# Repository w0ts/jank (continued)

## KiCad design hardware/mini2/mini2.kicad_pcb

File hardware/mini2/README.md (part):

# Jank mini 2.2: one board, two orders (USB only, or with a 1S cell), two MIDI OUTs, LINE IN with plug detect, CLOCK / RESET outs, a D-pad over 4 buttons, LEDs or a screen, u.FL (branch hw/mini2.2)

**Stage 2 + review pass 1 (2026-11-15, 72 x 72 mm): placed, routed, simulated, the fab files written; NOT ordered, NOT built, NOT measured.**
`mini2.kicad_pcb` is the routed board; `fab/` holds the Gerbers and both orders' BOM / CPL; `sim/` the simulations;
`case/` the case. Each stage's section supersedes the older ones where they differ (2, 1f, 1e, 1d, then 1c); "mini 2.2
(stage 1)" and "1b" are superseded (the encoder and the RGB LEDs are gone); everything after them is mini 2's text.

## Signoff3 (2026-11-17): round 3's fixes (`signoff2.py` again, `fatten.py`)

- **R2:** R136 is now 22 k. V5A is 4.79 V nominal, 4.58 .. 4.99 V over tolerances (the 74AHCT04 needs 4.5 V).
- **R3:** BAT_P / BAT_C / BAT_N widened up to 1 mm where room allows, with up to 3 vias at each layer change.
- **R4:** C3 is now 22 uF 25 V 0805.
- **R6:** the MIDI sinks Q10..Q13 are now AO3400A, which turn fully on from a 3.3 V gate.
- **R8:** the cell divider R10 / R11 is now 1 M / 1 M. The board drains ~9 .. 17 uA while switched off, against ~50 uA
  before. The cell reading then needs a firmware fix: board.h must read GPIO10, and the correction is affine, not an
  offset (REVIEW.md section 9).
- **R10:** R155's pads now sit 1.46 mm from the bottom edge (were 0.31 mm). R156, the same 1 ohm, is in parallel with
  it (at x 2.2, y 61.5: the only free spot): the bulk's series resistance is now 0.5 ohm, so a stiff USB cable rings VREG
  to ~5.3 V, not 5.8 V.
- **After fitting a cell,** or if the board is dead on the cell: plug USB in once. The XB5353A may hold a new cell off
  until a charger is connected, and also after a short.
- **For storage, unplug the cell.** Even switched off, the board draws a few uA from it.

## Sign-off stage 2 (2026-11-17): applied to the routed board (`signoff2.py`)

The stage-1 sign-off (`~/GitHub/jank/worktrees/mini22-review-scratch/REVIEW.md`) and its fixes:
- **R1:** C72 / C92 (2 x 100 uF) moved from VSYS to VREG, after the power switch, in both orders, behind R155 (1 ohm
  0805). Sim: VREG <= 5.16 V at switch-on and hot plug (was up to 7.9 V).
- **Inrush (usb order):** ~555 uC per plug (USB 2.0 asks 50 uC; 145 uC before). A host port's rail dips ~0.94 V for
  ~0.1 ms; another device on a bus-powered hub may reset. All of it passes R62 (0402, 0 ohm, ~14 A peak).
- **R6:** C104 (10 uF 0402) at U18's VIN. VBUS no longer runs on the bottom under U2, L4 or C5; it still skirts C3.
- **C2:** C97 / C103 added. Each LED now has its own 100 nF (C96, C97, C102, C103).
- **R5 not done:** CC2, UDP's via and CC1's via stay under J1's shell. The router found no way out (`signoff2.py`).
- **VSYS / VBUS:** with the toggle off, VSYS has no capacitance; a hot plug rings it to ~6.3 V. Add no part rated
  6 V or less there.
- **Never two cells.** J8 and J9 are in parallel before Q2 and the XB5353A. Q2 does not protect one cell from the
  other: a reversed or unequal second cell shorts or equalises through the sockets. Fit one cell in one socket.
- **Meter before soldering:** the DIN-504B (pad 2 = DIN 5, pad 4 = DIN 4), the PJ-307C (tip = pad 5) and each cell
  lead (+ on the square pad).
- **JP1 / JP2:** bridge one side only (G or V). GND is on one end and +3V3 on the other; a blob across all three pads
  shorts the rail.

## DIN-504B-M10 and PJ-320A pinouts: checked on paper (2026-11-15), confirm with a meter

Review pass 1's M5. A pinout agent checked the makers' drawings, EasyEDA's footprints, independent SDS-50J footprints
and CA-033 / DIN 41524, counting the bottom-side flip once (pictures: `~/GitHub/jank/worktrees/pinout-scratch/out/`).
Its verdict: **all correct**, so no swap jumpers.
- **DIN-504B-M10 (J5 / J6):** DIN 4 = pad 4 (the source, MD_R / MD2_R), DIN 5 = pad 2 (the sink, MD_T / MD2_T), DIN 2 =
  pad 3 (GND); pad 1 = DIN 3, pad 5 = DIN 1, pads 6 / 7 the shell.
- **PJ-320A (J13 CLOCK, J14 RESET):** the tip = contact D (CLK_OUT / RST_OUT), A = the sleeve (GND); **B is a second
  ring spring, not a switch**; C the ring.
- **PJ-307C:** the tip = pad 5, the ring = pad 2 (Type A), LINE IN's detect switch as wired.
- Still worth a meter on the first socket and jack before soldering a batch.

## Before ordering (checklist)

- The DIN / PJ-320A pinouts above: a meter on the first socket and jack.
- **JLC's placement preview** (review pass 1, LOW 9): the orientation of every IC (U1 the module, U2, U5, U6, U7, U8, U9,
  U11, U12, U15 .. U19, U21), FET (Q2 .. Q13), diode (D3, D7 .. D11, D14, D16), LED (LED1 .. LED4), L4 / L5 and J1, before paying.
- `sh case/make_stl.sh` re-run on the final board before printing (review pass 1, LOW 5: **not re-run** this round (the coordinator: the STLs come later); J4 moved under the RF line, the case reads it (`place_args.py`)).
- **Check every cell's polarity** with a meter (pin 1, the square pad, = +) before plugging it: see "a reversed cell"
  below.
- The tantalums C86 (+3V3, battery order), C27 and C91 (VBUS): JLC's preview must show their band (+) on pad 1.
- The firmware (review passes 1 and 2, updated 2026-11-15): the brown-out detector on; **the cell "empty" at 3.3 V
  under load** (the TPS63802 buck-boost holds +3V3 to the end: sim/power.py; the 3.6 V / 3.7 V rules and the 2.42"
  switch-on rule are gone with the LDO); **the USB pull-up (D+) only while VBUS_SENSE (GPIO14) is high** (Espressif's
  self-powered device rule); the cell's ADC reading calibrated once per board against a meter.
- **The firmware, 2026-11-15 (required changes):**
  - **Flash: the WROOM-1U-N8R2 has 8 MB** (+ 2 MB quad PSRAM for the heap, BLE MIDI): usbaudio's `partitions_usb.csv`
    (2 x 2 MB OTA slots + a 2 MB FAT drive, 6.1 MB) fits again; the FH4R2's 4 MB plan (streaming the drive into the spare
    slot) is no longer needed. Today's images: 1.05 MB (build-xiao), 1.28 MB with BLE.
  - **LED_DATA is GPIO38** (2026-11-15 GPIO re-map: "The GPIO map" is the pin map).
  - **The digital LINE IN** (2026-11-15): the ADC's continuous pattern at 83,333 Hz with 12 entries,
    **[tip, sense] x 5 + [tip, cell]**: tip = GPIO9 (ADC1_CH8, node A), sense = GPIO8 (ADC1_CH7, node B), cell = GPIO10
    (ADC1_CH9); ATTEN3 (0 .. 2.9 V; both nodes centred at 1.467 V). The signal is A - B: **the sense samples are skewed
    by one ADC slot against tip: correct them with a 16-tap half-sample delay filter**; **subtract each slot's own offset**
    (A and B's DC from the bias, measured with no plug or averaged); **interpolate the missing sense sample** in the
    [tip, cell] slot; an optional per-board gain calibration (A against B, a test tone on the sleeve). The tip runs at
    41.7 kHz, the sense at 34.7 kHz; the anti-alias pole 13.3 kHz (-5.4 dB at 20.8 kHz). LIN_DET (GPIO48).
  - **The RGB LEDs** (GPIO38, WS2812B-2020 GRB, 800 kHz: RMT) run from the 5 V aux rail (VLED ~4.9 V): no dropout rule.
  - **MIDI OUT: invert the UART TX** (`uart_set_line_inverse(port, UART_SIGNAL_TXD_INV)` on UART1 / GPIO37 and UART2 /
    GPIO42): the pins drive the 2N7002s of the 5 V loops (idle low = no current). Drive strength no longer matters. If
    the escape hatch back to the 3.3 V drive is used (R122 / R123, R126 .. R129), un-invert it.
  - **The 5 V aux rail** (U18, the TPS61023): **GPIO41 (V5_EN_IO) switches it**; R131 100 k to +3V3 keeps it ON while
    the pin floats (reset, boot, erased firmware). Drive it low to turn the LEDs, the MIDI loops, CLOCK / RESET and the
    host signal off (at the cell's cutoff, in sleep: `gpio_hold_en` + `gpio_deep_sleep_hold_en`, GPIO41 is not an RTC
    pin). Hatch: lift R137 (0 ohm) and the rail is on for good. Turn it off only with HOST_EN low and the LEDs dark.
    **The charge pump is gone: no LEDC on GPIO35 (pump.c), no pump warm-up**; CLK / RST can be driven at once (0 / ~4.4 V
    into 10 k, ~4.85 V into 100 k: sim/cv.txt; the user accepts it in place of the earlier "5 V+" rule).
  - **USB host mode (battery order only):** the TUSB320LI at I2C 0x47 starts as a sink (PORT low). For host mode write
    DRP + Try.SRC (MODE_SELECT, SOURCE_PREF) with DISABLE_TERM set around it (its 7.3.2 sequence); on INT (GPIO13,
    pull-up on) read ATTACHED_STATE: **Attached.SRC (a device) -> HOST_EN (GPIO47) high and the S3's USB-OTG in host
    mode; anything else (detached, Attached.SNK: a charger or a host) -> HOST_EN low first**, then device mode. V5H comes
    from the 5 V aux rail (no pump): **usbport's prep_ms ~0** (the aux rail is already up; the TPS61023's soft start is
    ~0.7 ms after the switch-on: its sheet). HOST_EN never high while unattached (Type-C: no VBUS before an attach). Device mode keeps the review-pass-2 rules (VBUS_SENSE, the D+ pull-up). The
    usb order has no U17 / Q9 (R3 / R4 / R63 fitted): device only.

## Experiment A (2026-11-15, the user's: "fewer part types, no change to how the circuit works")

On Standard every part type pays JLC's loading fee (~$1.53; the quote's $88.35 = 57 types), so the lever is the type
count. Each merge checked against the datasheets and the sims (`sim/`):

| Merge | Verdict |
|---|---|
| R51 12 k 0603 -> 0402 (C25752) | applied |
| R120 / R121 47 ohm 0603 -> 100 ohm 0402 (C25076) | applied; `cv.py` (the sleeve 100 ohm): 4.36 V into 10 k (typ), 4.79 V into 100 k |
| R40 33 -> 22 ohm (C25092) | applied |
| R88 / R89 22 k / 33 k -> 100 k / 150 k | applied; `power.py`: Q1 back on 0.30 .. 0.52 s after an unplug (was 0.16 .. 0.28: VBUS decays slower), D9 carries meanwhile, VSYS min unchanged |
| R136 18 k -> 20 k | applied: V5A 4.85 V (4.72 .. 4.97). `cv.py` 4.36 / 4.25 V into 10 k (was 4.44, the user accepted ~4.5), `midi.py` 5.24 mA typical (5.51), 3.37 mA at the worst corner (3.54), `host.py` 4.40 V into 100 k (4.46); the clamp's overlap with the boost 2 mA at most (was 7) |
| R141 56 k -> 100 k + 12 k (R146), R142 10 k -> 20 k | applied: 3.30 V, R2 20 k (TI: <= 100 k) |
| jack sources 3 x 680 -> 2 x 470; the four 220 ohm sinks -> 470 // 470 (R147 .. R150) | applied; `midi.py` above |
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
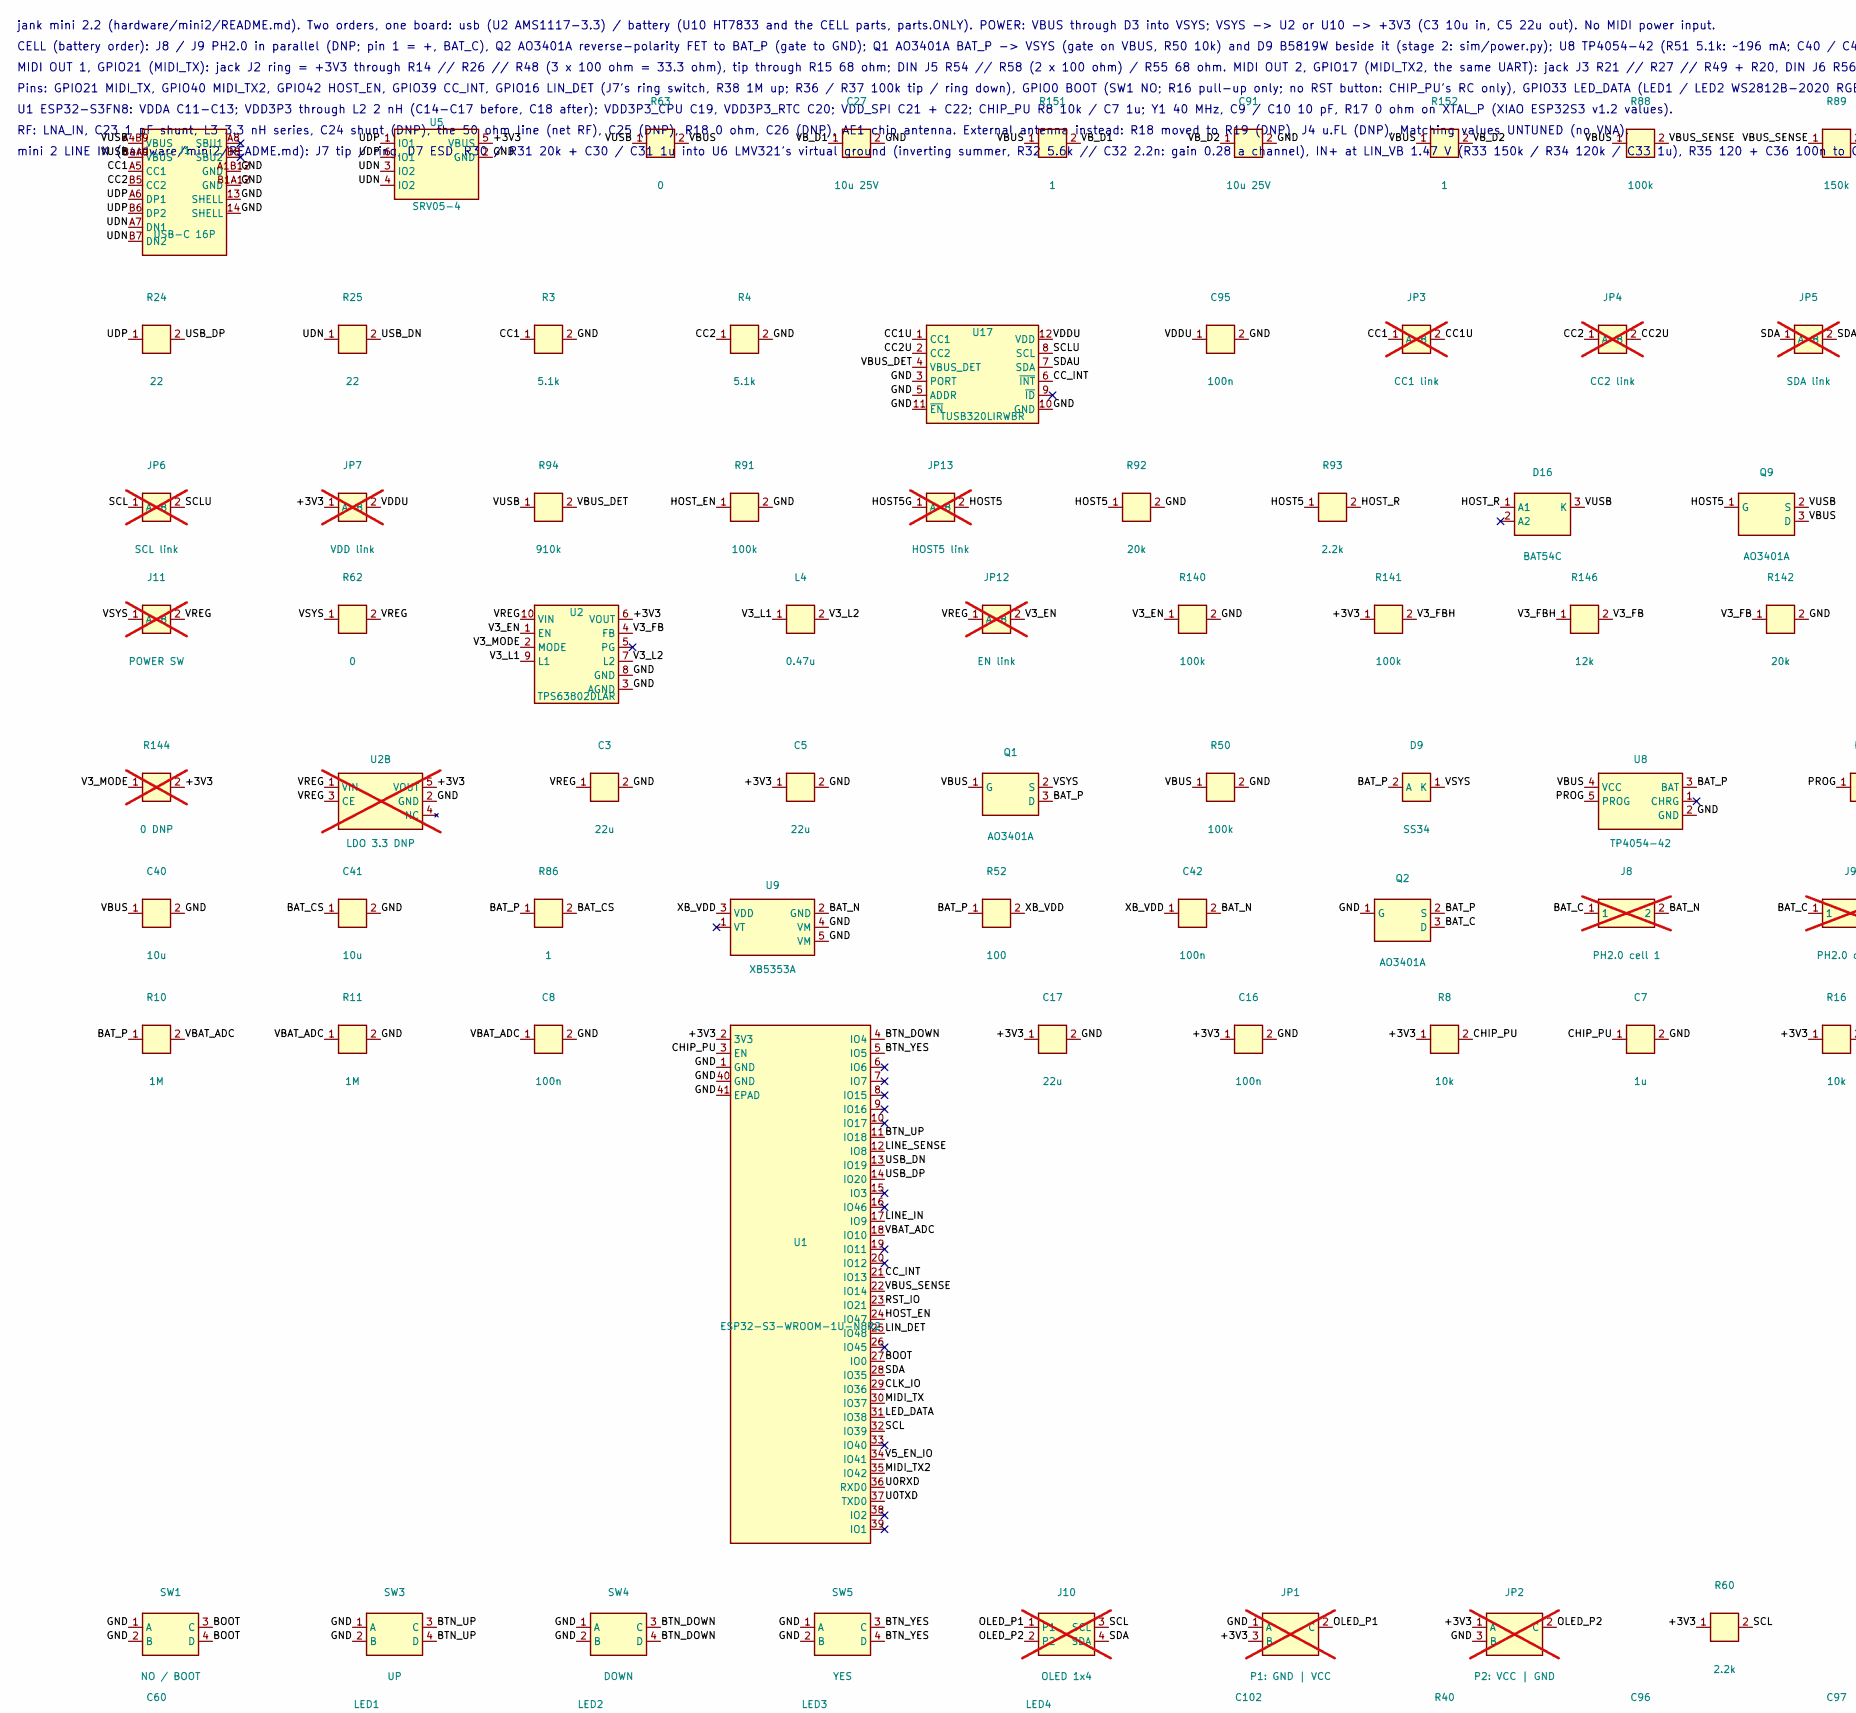
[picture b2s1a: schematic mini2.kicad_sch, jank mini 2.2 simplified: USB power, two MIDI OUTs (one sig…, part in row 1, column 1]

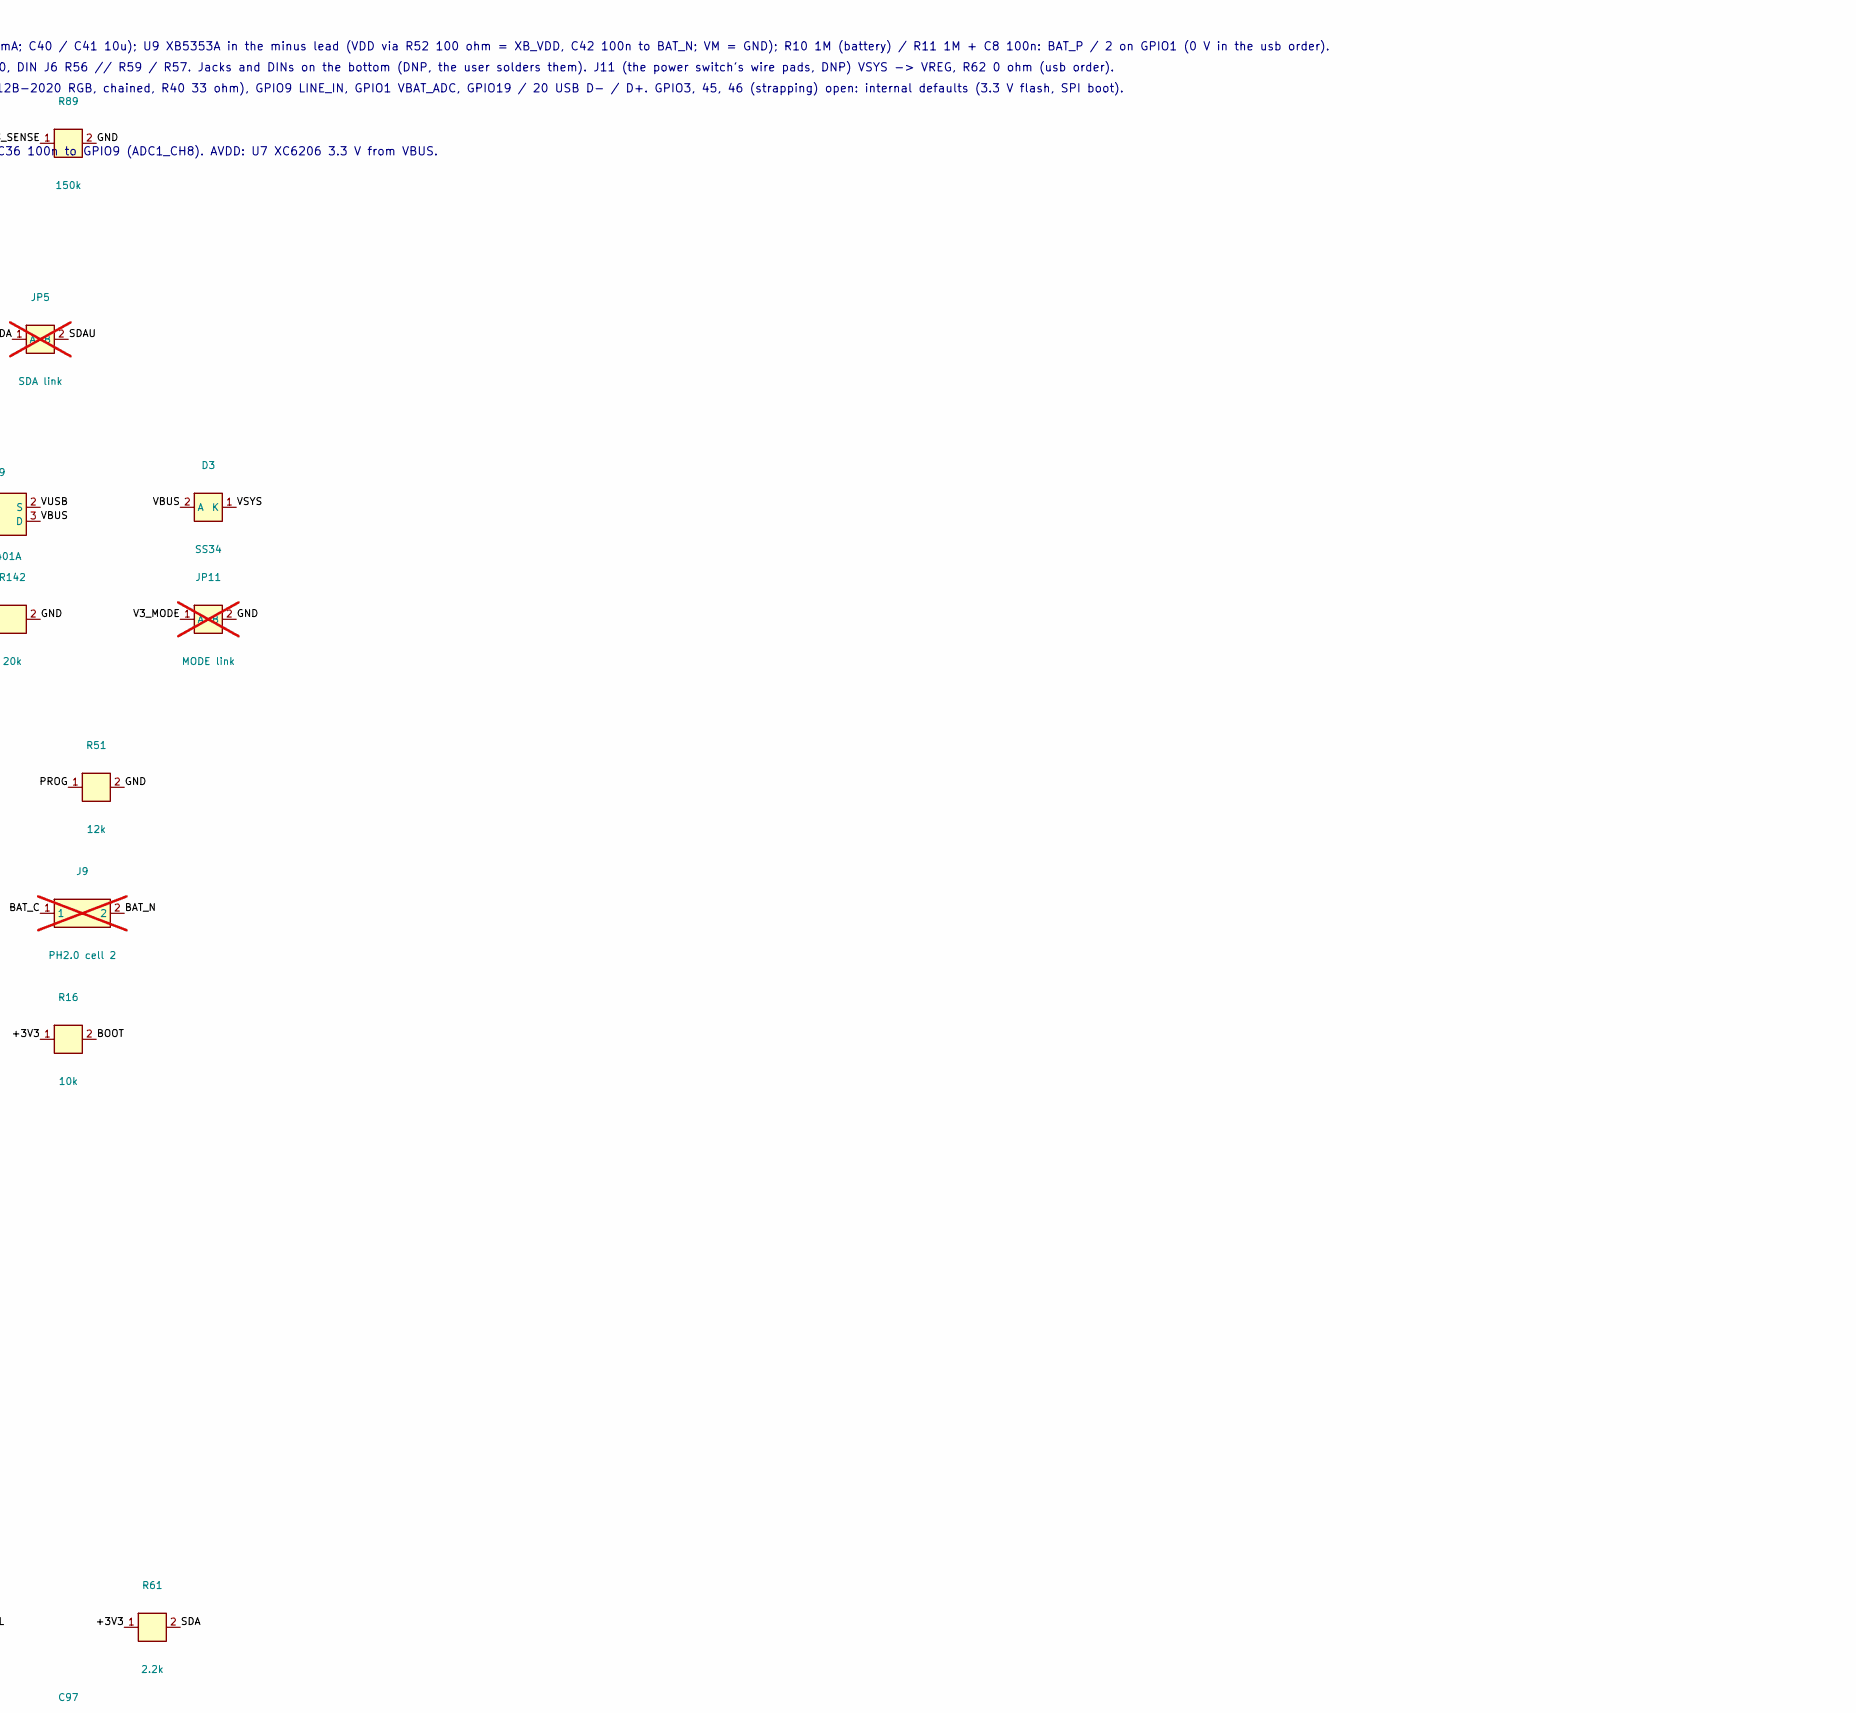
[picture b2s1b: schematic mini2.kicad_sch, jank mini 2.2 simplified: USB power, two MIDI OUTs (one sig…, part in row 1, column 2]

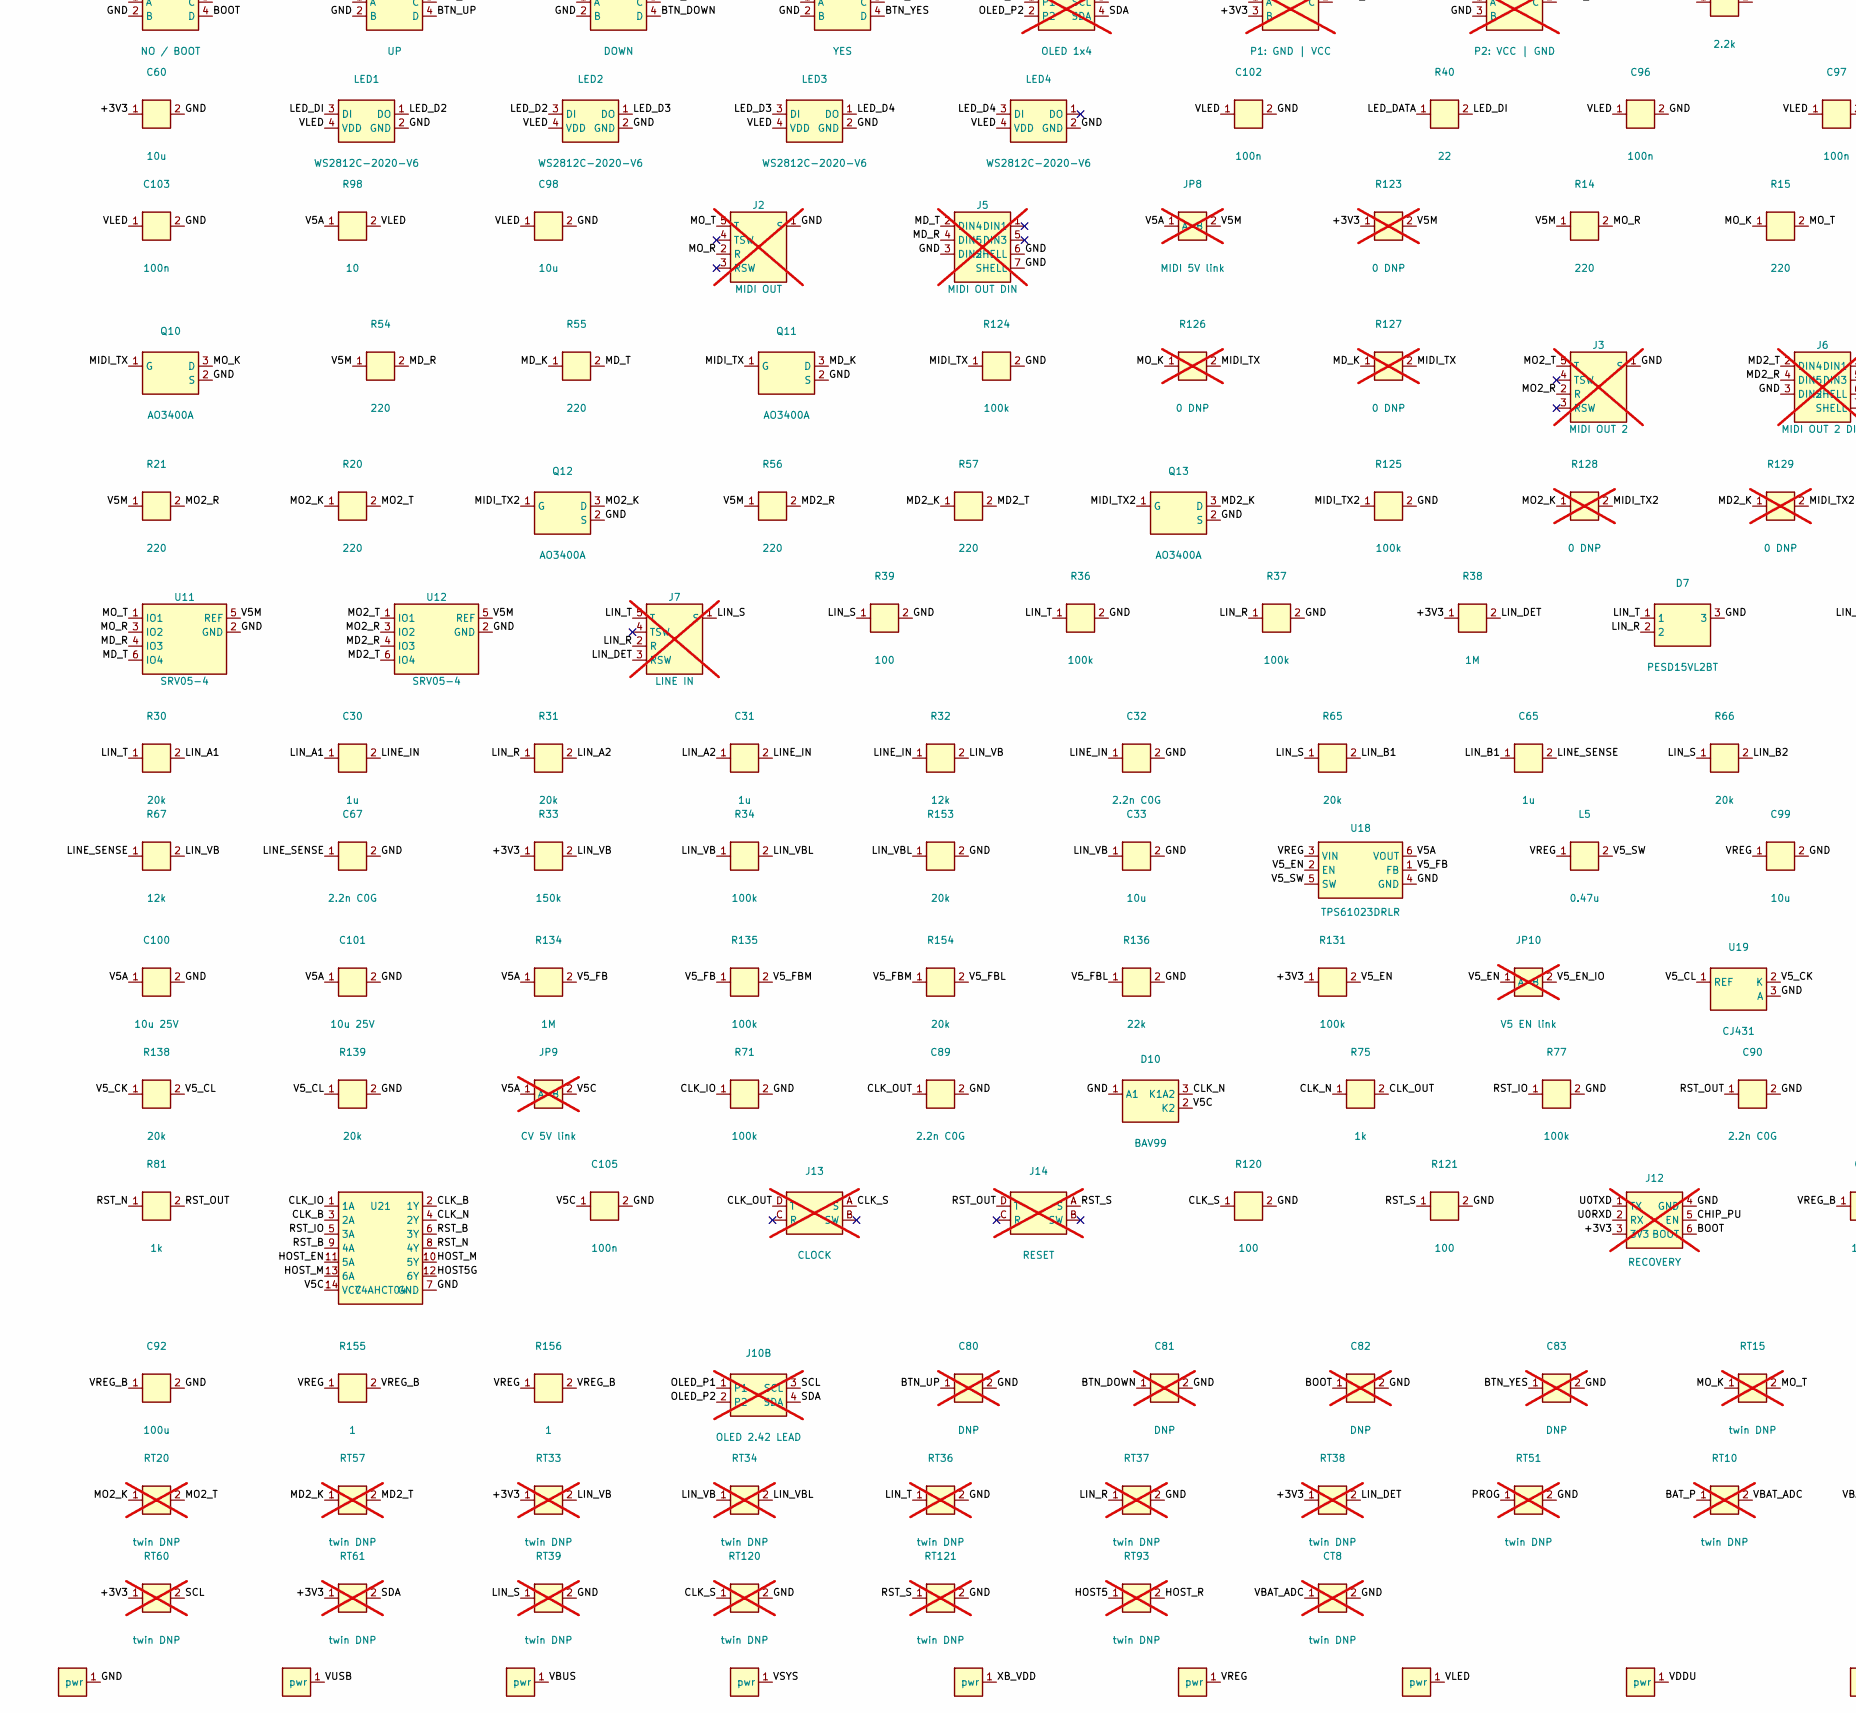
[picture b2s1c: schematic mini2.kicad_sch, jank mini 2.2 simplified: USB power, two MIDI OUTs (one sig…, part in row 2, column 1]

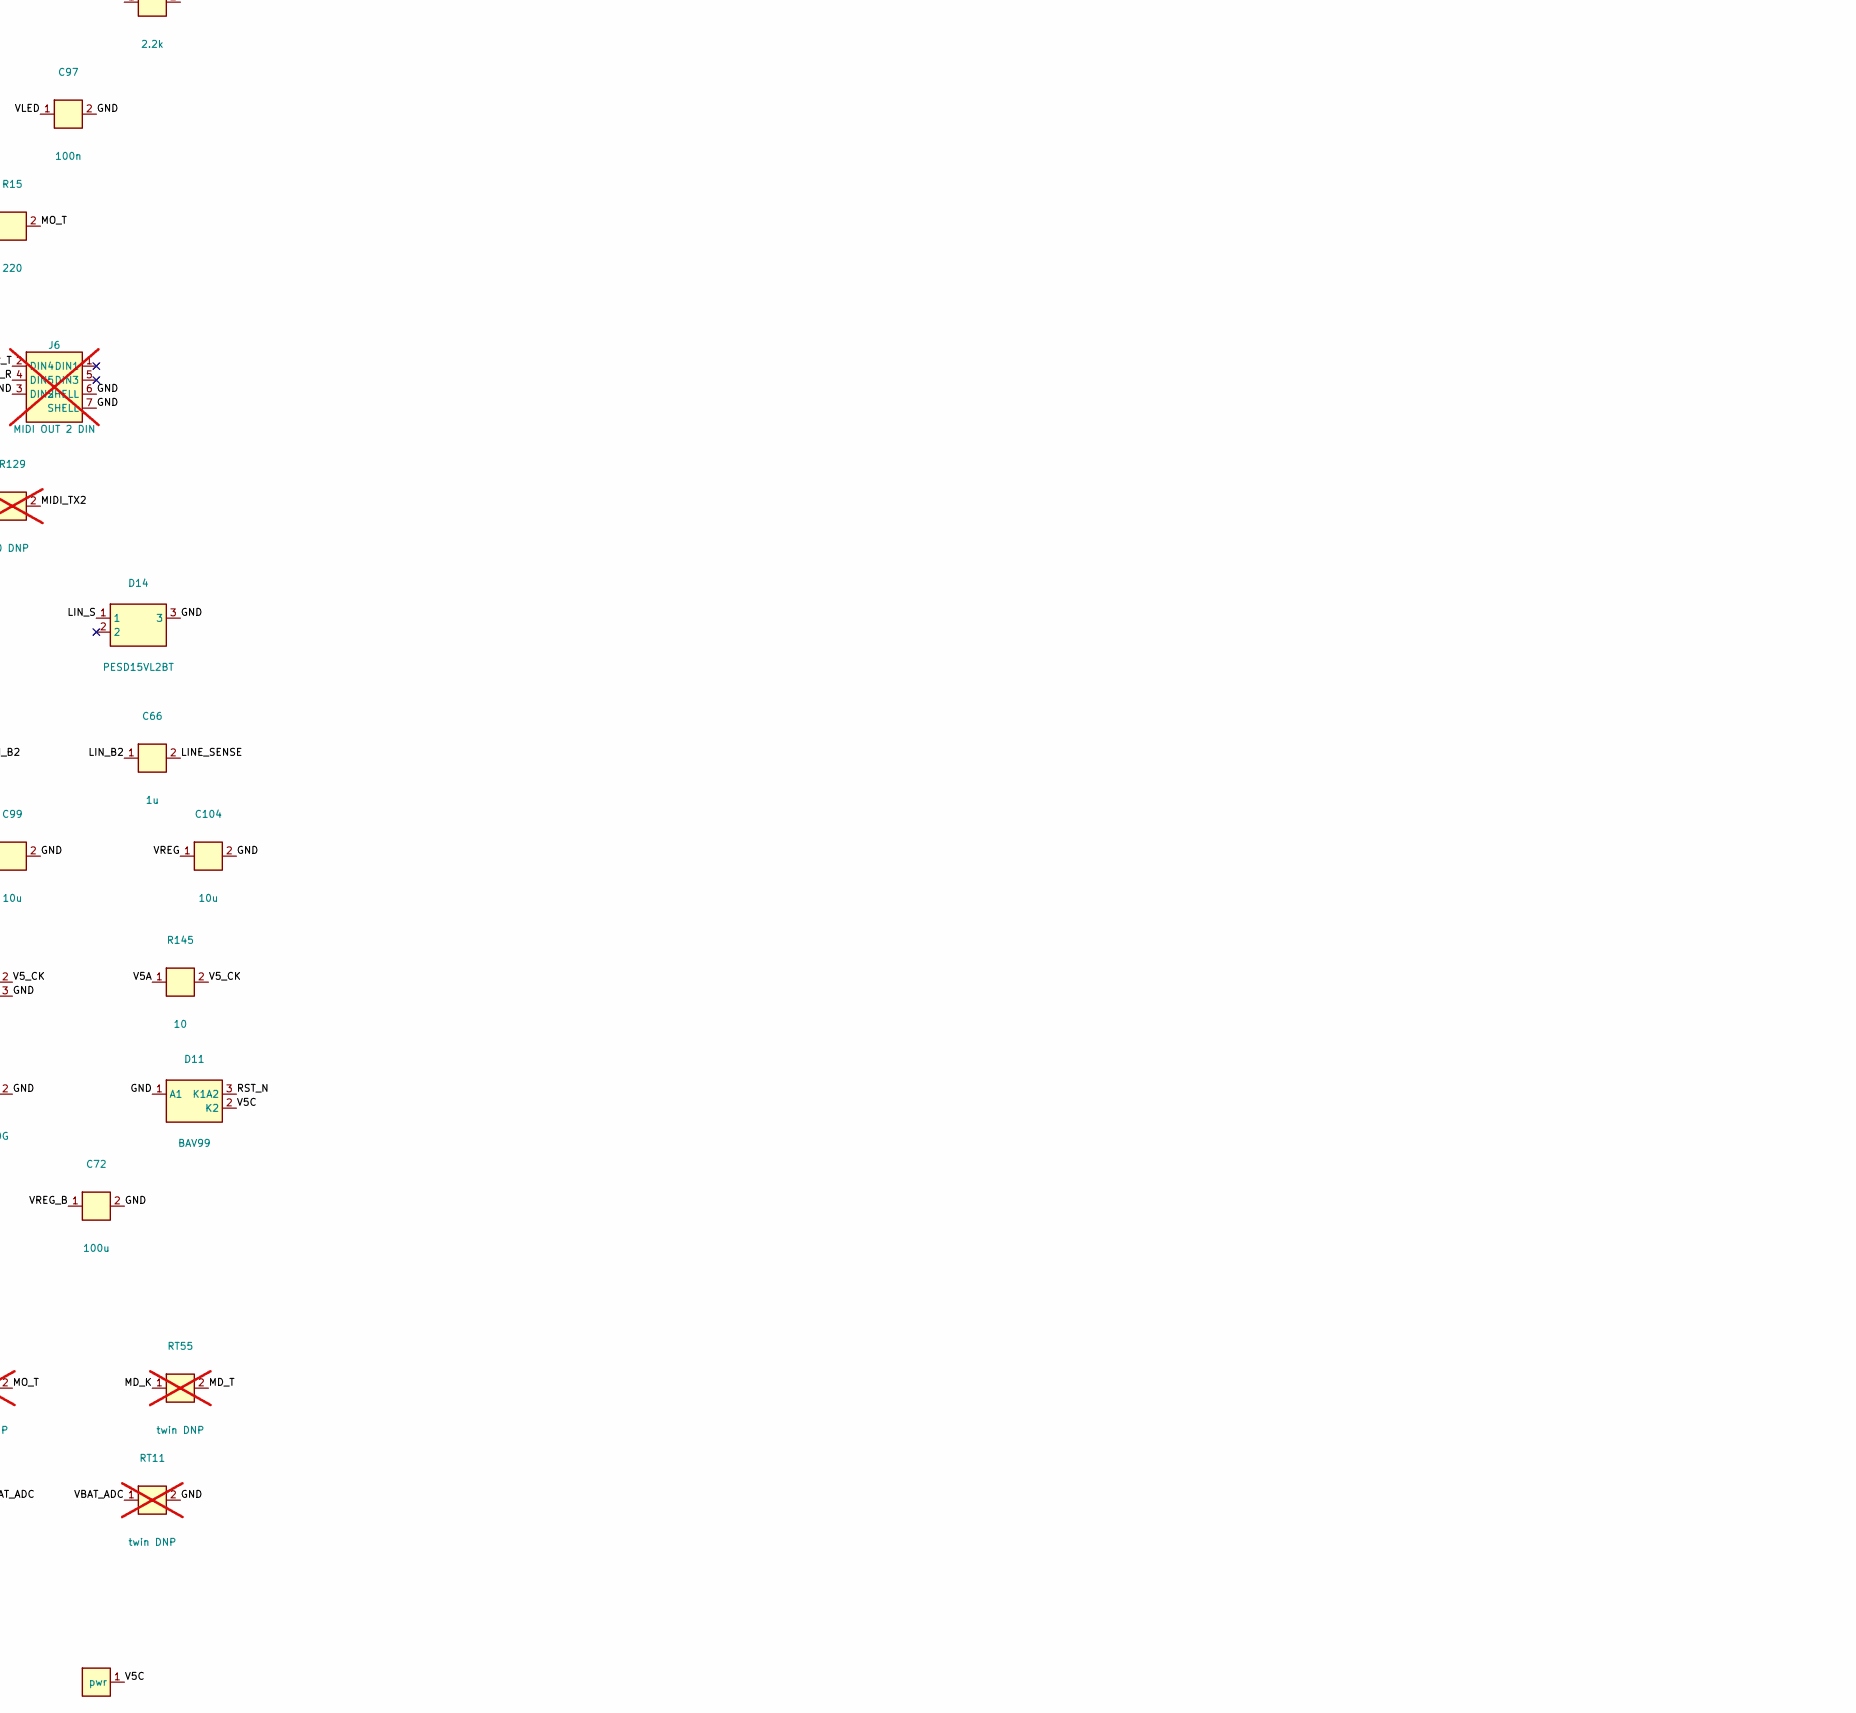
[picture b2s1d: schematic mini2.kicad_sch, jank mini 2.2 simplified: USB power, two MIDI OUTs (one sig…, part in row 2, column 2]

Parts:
C3: 22u; C0805; LCSC C45783
C5, C17: 22u; C0603; LCSC C59461
C7, C30, C31, C65, C66: 1u; C0402; LCSC C52923
C8, C16, C42, C95, C96, C97, C102, C103, C105: 100n; C0402; LCSC C1525
C27, C91, C100, C101: 10u 25V; C0805; LCSC C15850
C32, C67, C89, C90: 2.2n C0G; C0603; LCSC C2991172
C33, C40, C41, C60, C98, C99: 10u; C0603; LCSC C19702
C72, C92: 100u; C1206; LCSC C15008
C80, C81, C82, C83: DNP; C0603; not fitted
C104: 10u; C0402; LCSC C15525
CT8: twin DNP; C_TWIN_HAND; not fitted
D3, D9: SS34; SMA_L4.3-W2.6-LS5.2-RD; LCSC C8678
D7, D14: PESD15VL2BT; SOT-23_L2.9-W1.3-P1.90-LS2.4-BR; LCSC C38838
D10, D11: BAV99; SOT-23_L2.9-W1.3-P1.90-LS2.4-BR; LCSC C2500
D16: BAT54C; SOT-23-3_L2.9-W1.6-P1.90-LS2.8-BR; LCSC C37704
J1: USB-C 16P; USB-C-SMD_TYPE-C-16PIN-2MD-073; LCSC C2765186
J2: MIDI OUT; AUDIO-TH_PJ307C; LCSC C16684; not fitted
J3: MIDI OUT 2; AUDIO-TH_PJ307C; LCSC C16684; not fitted
J5: MIDI OUT DIN; CONN-TH_DIN-504B-M10; LCSC C2939346; not fitted
J6: MIDI OUT 2 DIN; CONN-TH_DIN-504B-M10; LCSC C2939346; not fitted
J7: LINE IN; AUDIO-TH_PJ307C; LCSC C16684; not fitted
J8: PH2.0 cell 1; CONN-TH_B2B-PH-K-S; LCSC C131337; not fitted
J9: PH2.0 cell 2; CONN-TH_B2B-PH-K-S; LCSC C131337; not fitted
J10: OLED 1x4; HDR-TH_4P-P2.54-V-M; LCSC C2691448; not fitted
J10B: OLED 2.42 LEAD; HDR-TH_4P-P2.54-V-M; not fitted
J11: POWER SW; PADS2_HAND; not fitted
J12: RECOVERY; PADS6_SMD; not fitted
J13: CLOCK; AUDIO-TH_PJ-320A-4P-DIP; LCSC C18185602; not fitted
J14: RESET; AUDIO-TH_PJ-320A-4P-DIP; LCSC C18185602; not fitted
JP1: P1: GND | VCC; SJ3_SMD; not fitted
JP2: P2: VCC | GND; SJ3_SMD; not fitted
JP3: CC1 link; SJ2C_SMD; not fitted
JP4: CC2 link; SJ2C_SMD; not fitted
JP5: SDA link; SJ2C_SMD; not fitted
JP6: SCL link; SJ2C_SMD; not fitted
JP7: VDD link; SJ2C_SMD; not fitted
JP8: MIDI 5V link; SJ2C_SMD; not fitted
JP9: CV 5V link; SJ2C_SMD; not fitted
JP10: V5 EN link; SJ2C_SMD; not fitted
JP11: MODE link; SJ2C_SMD; not fitted
JP12: EN link; SJ2C_SMD; not fitted
JP13: HOST5 link; SJ2C_SMD; not fitted
L4, L5: 0.47u; IND-SMD_L2.0-W1.6-1; LCSC C668312
LED1, LED2, LED3, LED4: WS2812C-2020-V6; LED-SMD_4P-L2.2-W2.0-P1.00_WS2815C-2020-4P; LCSC C55109522
Q1, Q2, Q9: AO3401A; SOT-23_L2.9-W1.3-P1.90-LS2.4-BR; LCSC C15127
Q10, Q11, Q12, Q13: AO3400A; SOT-23_L2.9-W1.3-P1.90-LS2.4-BR; LCSC C20917
R3, R4: 5.1k; R0603; LCSC C23186
R8, R16: 10k; R0402; LCSC C25744
R10, R11, R38, R134: 1M; R0402; LCSC C26083
R14, R15, R20, R21, R54, R55, R56, R57: 220; R1206; LCSC C17957
R24, R25, R40: 22; R0402; LCSC C25092
R30, R31, R65, R66, R92, R138, R139, R142, R153, R154: 20k; R0402; LCSC C25765
R32, R51, R67, R146: 12k; R0402; LCSC C25752
R33, R89: 150k; R0402; LCSC C25755
R34, R36, R37, R50, R71, R77, R88, R91, R124, R125, R131, R135, R140, R141: 100k; R0402; LCSC C25741
R39, R52, R120, R121: 100; R0402; LCSC C25076
R60, R61, R93: 2.2k; R0402; LCSC C25879
R62: 0; R0402; LCSC C17168
R63: 0; R0603; LCSC C21189
R75, R81: 1k; R1206; LCSC C4410
R86, R151, R152: 1; R0402; LCSC C25086
R94: 910k; R0402; LCSC C25800
R98, R145: 10; R0402; LCSC C25077
R123, R126, R127, R128, R129, R144: 0 DNP; R0402; not fitted
R136: 22k; R0402; LCSC C25768
R155, R156: 1; R0805; LCSC C25271
RT10, RT11, RT15, RT20, RT33, RT34, RT36, RT37, RT38, RT39, RT51, RT55, RT57, RT60, RT61, RT93, RT120, RT121: twin DNP; R_TWIN_HAND; not fitted
SW1: NO / BOOT; SW-SMD_4P-L5.1-W5.1-P3.70-LS6.5-TL_H1.5; LCSC C318884
SW3: UP; SW-SMD_4P-L5.1-W5.1-P3.70-LS6.5-TL_H1.5; LCSC C318884
SW4: DOWN; SW-SMD_4P-L5.1-W5.1-P3.70-LS6.5-TL_H1.5; LCSC C318884
SW5: YES; SW-SMD_4P-L5.1-W5.1-P3.70-LS6.5-TL_H1.5; LCSC C318884
U1: ESP32-S3-WROOM-1U-N8R2; WIRELM-SMD_ESP32-S3-WROOM-1U; LCSC C3013944
U2: TPS63802DLAR; VSON-10_L3.0-W2.0-P0.50-TL; LCSC C2845237
U2B: LDO 3.3 DNP; SOT-23-5_L3.0-W1.7-P0.95-LS2.8-BR; not fitted
U5, U11, U12: SRV05-4; SOT-23-6_L2.9-W1.6-P0.95-LS2.8-BL-1; LCSC C7420376
U8: TP4054-42; SOT-23-5_L3.0-W1.7-P0.95-LS2.8-BL; LCSC C32574
U9: XB5353A; SOT-23-5_L3.0-W1.7-P0.95-LS2.8-BR; LCSC C80628
U17: TUSB320LIRWBR; X2QFN-12_L1.6-W1.6-P0.40-TL; LCSC C2836598
U18: TPS61023DRLR; SOT-563_L1.6-W1.2-P0.50-LS1.6-BR; LCSC C919459
U19: CJ431; SOT-23-3_L2.9-W1.6-P1.90-LS2.8-BR; LCSC C3113
U21: 74AHCT04; TSSOP-14_L5.0-W4.4-P0.65-LS6.4-BL; LCSC C8190

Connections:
+3V3: C5.1, C16.1, C17.1, C60.1, J12.3 (3V3), JP1.3 (B), JP2.1 (A), JP7.1 (A), R8.1, R16.1, R33.1, R38.1, R60.1, R61.1, R123.1, R131.1, R141.1, R144.2, RT33.1, RT38.1, RT60.1, RT61.1, U1.2 (3V3), U2.6 (VOUT), U2B.5 (VOUT), U5.5 (VBUS)
BAT_C: J8.1, J9.1, Q2.3 (D)
BAT_CS: C41.1, R86.2
BAT_N: C42.2, J8.2, J9.2, U9.2 (GND)
BAT_P: D9.2 (A), Q1.3 (D), Q2.2 (S), R10.1, R52.1, R86.1, RT10.1, U8.3 (BAT)
BOOT: C82.1, J12.6 (BOOT), R16.2, SW1.3 (C), SW1.4 (D), U1.27 (IO0)
BTN_DOWN: C81.1, SW4.3 (C), SW4.4 (D), U1.4 (IO4)
BTN_UP: C80.1, SW3.3 (C), SW3.4 (D), U1.11 (IO18)
BTN_YES: C83.1, SW5.3 (C), SW5.4 (D), U1.5 (IO5)
CC1: J1.A5 (CC1), JP3.1 (A), R3.1
CC1U: JP3.2 (B), U17.1 (CC1)
CC2: J1.B5 (CC2), JP4.1 (A), R4.1
CC2U: JP4.2 (B), U17.2 (CC2)
CC_INT: U1.21 (IO13), U17.6 (~INT)
CHIP_PU: C7.1, J12.5 (EN), R8.2, U1.3 (EN)
CLK_B: U21.2 (1Y), U21.3 (2A)
CLK_IO: R71.1, U1.29 (IO36), U21.1 (1A)
CLK_N: D10.3 (K1A2), R75.1, U21.4 (2Y)
CLK_OUT: C89.1, J13.D (T), R75.2
CLK_S: J13.A (S), R120.1, RT120.1
GND: C3.2, C5.2, C7.2, C8.2, C16.2, C17.2, C27.2, C32.2, C33.2, C40.2, C41.2, C60.2, C67.2, C72.2, C80.2, C81.2, C82.2, C83.2, C89.2, C90.2, C91.2, C92.2, C95.2, C96.2, C97.2, C98.2, C99.2, C100.2, C101.2, C102.2, C103.2, C104.2, C105.2, CT8.2, D7.3, D10.1 (A1), D11.1 (A1), D14.3, J1.13 (SHELL), J1.14 (SHELL), J1.A1B12 (GND), J1.B1A12 (GND), J2.1 (S), J3.1 (S), J5.3 (DIN2), J5.6 (SHELL), J5.7 (SHELL), J6.3 (DIN2), J6.6 (SHELL), J6.7 (SHELL), J12.4 (GND), JP1.1 (A), JP2.3 (B), JP11.2 (B), LED1.2 (GND), LED2.2 (GND), LED3.2 (GND), LED4.2 (GND), Q2.1 (G), Q10.2 (S), Q11.2 (S), Q12.2 (S), Q13.2 (S), R3.2, R4.2, R11.2, R36.2, R37.2, R39.2, R50.2, R51.2, R71.2, R77.2, R89.2, R91.2, R92.2, R120.2, R121.2, R124.2, R125.2, R136.2, R139.2, R140.2, R142.2, R153.2, RT11.2, RT36.2, RT37.2, RT39.2, RT51.2, RT120.2, RT121.2, SW1.1 (A), SW1.2 (B), SW3.1 (A), SW3.2 (B), SW4.1 (A), SW4.2 (B), SW5.1 (A), SW5.2 (B), U1.1 (GND), U1.40 (GND), U1.41 (EPAD), U2.3 (AGND), U2.8 (GND), U2B.2 (GND), U5.2 (GND), U8.2 (GND), U9.4 (VM), U9.5 (VM), U11.2 (GND), U12.2 (GND), U17.3 (PORT), U17.5 (ADDR), U17.10 (GND), U17.11 (~EN), U18.4 (GND), U19.3 (A), U21.7 (GND)
HOST5: JP13.2 (B), Q9.1 (G), R92.1, R93.1, RT93.1
HOST5G: JP13.1 (A), U21.12 (6Y)
HOST_EN: R91.1, U1.24 (IO47), U21.11 (5A)
HOST_M: U21.10 (5Y), U21.13 (6A)
HOST_R: D16.1 (A1), R93.2, RT93.2
LED_D2: LED1.1 (DO), LED2.3 (DI)
LED_D3: LED2.1 (DO), LED3.3 (DI)
LED_D4: LED3.1 (DO), LED4.3 (DI)
LED_DATA: R40.1, U1.31 (IO38)
LED_DI: LED1.3 (DI), R40.2
LINE_IN: C30.2, C31.2, C32.1, R32.1, U1.17 (IO9)
LINE_SENSE: C65.2, C66.2, C67.1, R67.1, U1.12 (IO8)
LIN_A1: C30.1, R30.2
LIN_A2: C31.1, R31.2
LIN_B1: C65.1, R65.2
LIN_B2: C66.1, R66.2
LIN_DET: J7.3 (RSW), R38.2, RT38.2, U1.25 (IO48)
LIN_R: D7.2, J7.2 (R), R31.1, R37.1, RT37.1
LIN_S: D14.1, J7.1 (S), R39.1, R65.1, R66.1, RT39.1
LIN_T: D7.1, J7.5 (T), R30.1, R36.1, RT36.1
LIN_VB: C33.1, R32.2, R33.2, R34.1, R67.2, RT33.2, RT34.1
LIN_VBL: R34.2, R153.1, RT34.2
MD2_K: Q13.3 (D), R57.1, R129.1, RT57.1
MD2_R: J6.4 (DIN5), R56.2, U12.4 (IO3)
MD2_T: J6.2 (DIN4), R57.2, RT57.2, U12.6 (IO4)
MD_K: Q11.3 (D), R55.1, R127.1, RT55.1
MD_R: J5.4 (DIN5), R54.2, U11.4 (IO3)
MD_T: J5.2 (DIN4), R55.2, RT55.2, U11.6 (IO4)
MIDI_TX: Q10.1 (G), Q11.1 (G), R124.1, R126.2, R127.2, U1.30 (IO37)
MIDI_TX2: Q12.1 (G), Q13.1 (G), R125.1, R128.2, R129.2, U1.35 (IO42)
MO2_K: Q12.3 (D), R20.1, R128.1, RT20.1
MO2_R: J3.2 (R), R21.2, U12.3 (IO2)
MO2_T: J3.5 (T), R20.2, RT20.2, U12.1 (IO1)
MO_K: Q10.3 (D), R15.1, R126.1, RT15.1
MO_R: J2.2 (R), R14.2, U11.3 (IO2)
MO_T: J2.5 (T), R15.2, RT15.2, U11.1 (IO1)
OLED_P1: J10.1, J10B.1, JP1.2 (C)
OLED_P2: J10.2, J10B.2, JP2.2 (C)
PROG: R51.1, RT51.1, U8.5 (PROG)
RST_B: U21.6 (3Y), U21.9 (4A)
RST_IO: R77.1, U1.23 (IO21), U21.5 (3A)
RST_N: D11.3 (K1A2), R81.1, U21.8 (4Y)
RST_OUT: C90.1, J14.D (T), R81.2
RST_S: J14.A (S), R121.1, RT121.1
SCL: J10.3 (SCL), J10B.3 (SCL), JP6.1 (A), R60.2, RT60.2, U1.32 (IO39)
SCLU: JP6.2 (B), U17.8 (SCL)
SDA: J10.4 (SDA), J10B.4 (SDA), JP5.1 (A), R61.2, RT61.2, U1.28 (IO35)
SDAU: JP5.2 (B), U17.7 (SDA)
U0RXD: J12.2 (RX), U1.36 (RXD0)
U0TXD: J12.1 (TX), U1.37 (TXD0)
UDN: J1.A7 (DN1), J1.B7 (DN2), R25.1, U5.3 (IO2), U5.4 (IO2)
UDP: J1.A6 (DP1), J1.B6 (DP2), R24.1, U5.1 (IO1), U5.6 (IO1)
USB_DN: R25.2, U1.13 (IO19)
USB_DP: R24.2, U1.14 (IO20)
V3_EN: JP12.2 (B), R140.1, U2.1 (EN)
V3_FB: R142.1, R146.2, U2.4 (FB)
V3_FBH: R141.2, R146.1
V3_L1: L4.1, U2.9 (L1)
V3_L2: L4.2, U2.7 (L2)
V3_MODE: JP11.1 (A), R144.1, U2.2 (MODE)
V5A: C100.1, C101.1, JP8.1 (A), JP9.1 (A), R98.1, R134.1, R145.1, U18.6 (VOUT)
V5C: C105.1, D10.2 (K2), D11.2 (K2), JP9.2 (B), U21.14 (VCC)
V5M: JP8.2 (B), R14.1, R21.1, R54.1, R56.1, R123.2, U11.5 (REF), U12.5 (REF)
V5_CK: R138.1, R145.2, U19.2 (K)
V5_CL: R138.2, R139.1, U19.1 (REF)
V5_EN: JP10.1 (A), R131.2, U18.2 (EN)
V5_EN_IO: JP10.2 (B), U1.34 (IO41)
V5_FB: R134.2, R135.1, U18.1 (FB)
V5_FBL: R136.1, R154.2
V5_FBM: R135.2, R154.1
V5_SW: L5.2, U18.5 (SW)
VBAT_ADC: C8.1, CT8.1, R10.2, R11.1, RT10.2, RT11.1, U1.18 (IO10)
VBUS: C40.1, D3.2 (A), Q1.1 (G), Q9.3 (D), R50.1, R63.2, R88.1, R151.1, R152.1, U8.4 (VCC)
VBUS_DET: R94.2, U17.4 (VBUS_DET)
VBUS_SENSE: R88.2, R89.1, U1.22 (IO14)
VB_D1: C27.1, R151.2
VB_D2: C91.1, R152.2
VDDU: C95.1, JP7.2 (B), U17.12 (VDD)
VLED: C96.1, C97.1, C98.1, C102.1, C103.1, LED1.4 (VDD), LED2.4 (VDD), LED3.4 (VDD), LED4.4 (VDD), R98.2
VREG: C3.1, C99.1, C104.1, J11.2 (B), JP12.1 (A), L5.1, R62.2, R155.1, R156.1, U2.10 (VIN), U2B.1 (VIN), U2B.3 (CE), U18.3 (VIN)
VREG_B: C72.1, C92.1, R155.2, R156.2
VSYS: D3.1 (K), D9.1 (K), J11.1 (A), Q1.2 (S), R62.1
VUSB: D16.3 (K), J1.A4B9 (VBUS), J1.B4A9 (VBUS), Q9.2 (S), R63.1, R94.1
XB_VDD: C42.1, R52.2, U9.3 (VDD)

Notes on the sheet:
jank mini 2.2 (hardware/mini2/README.md). Two orders, one board: usb (U2 AMS1117-3.3) / battery (U10 HT7833 and the CELL parts, parts.ONLY). POWER: VBUS through D3 into VSYS; VSYS -> U2 or U10 -> +3V3 (C3 10u in, C5 22u out). No MIDI power input.
CELL (battery order): J8 / J9 PH2.0 in parallel (DNP; pin 1 = +, BAT_C), Q2 AO3401A reverse-polarity FET to BAT_P (gate to GND); Q1 AO3401A BAT_P -> VSYS (gate on VBUS, R50 10k) and D9 B5819W beside it (stage 2: sim/power.py); U8 TP4054-42 (R51 5.1k: ~196 mA; C40 / C41 10u); U9 XB5353A in the minus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
MIDI OUT 1, GPIO21 (MIDI_TX): jack J2 ring = +3V3 through R14 // R26 // R48 (3 x 100 ohm = 33.3 ohm), tip through R15 68 ohm; DIN J5 R54 // R58 (2 x 100 ohm) / R55 68 ohm. MIDI OUT 2, GPIO17 (MIDI_TX2, the same UART): jack J3 R21 // R27 // R49 + R20, DIN J6 R56 // R59 / R57. Jacks and DINs on the b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
Pins: GPIO21 MIDI_TX, GPIO40 MIDI_TX2, GPIO42 HOST_EN, GPIO39 CC_INT, GPIO16 LIN_DET (J7's ring switch, R38 1M up; R36 / R37 100k tip / ring down), GPIO0 BOOT (SW1 NO; R16 pull-up only; no RST button: CHIP_PU's RC only), GPIO33 LED_DATA (LED1 / LED2 WS2812B-2020 RGB, chained, R40 33 ohm), GPIO9 LIN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
U1 ESP32-S3FN8: VDDA C11-C13; VDD3P3 through L2 2 nH (C14-C17 before, C18 after); VDD3P3_CPU C19, VDD3P3_RTC C20; VDD_SPI C21 + C22; CHIP_PU R8 10k / C7 1u; Y1 40 MHz, C9 / C10 10 pF, R17 0 ohm on XTAL_P (XIAO ESP32S3 v1.2 values).
RF: LNA_IN, C23 1 pF shunt, L3 3.3 nH series, C24 shunt (DNP), the 50 ohm line (net RF), C25 (DNP), R18 0 ohm, C26 (DNP), AE1 chip antenna. External antenna instead: R18 moved to R19 (DNP), J4 u.FL (DNP). Matching values UNTUNED (no VNA).
mini 2 LINE IN (hardware/mini2/README.md): J7 tip / ring, D7 ESD, R30 / R31 20k + C30 / C31 1u into U6 LMV321's virtual ground (inverting summer, R32 5.6k // C32 2.2n: gain 0.28 a channel), IN+ at LIN_VB 1.47 V (R33 150k / R34 120k / C33 1u), R35 120 + C36 100n to GPIO9 (ADC1_CH8). AVDD: U7 XC6206 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
